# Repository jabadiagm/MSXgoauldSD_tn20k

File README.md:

# MSXgoauldSD_tn20k (DirectVideo branch)
MSX Goa'uld board with Tang Nano 20k and SD support

MSX2+ engine in Z80 socket. It turns one MSX into an MSX2+ by replacing Z80 processor. FPGA in board contains: 
* Z80
* V9958 with hdmi output
* MSX2+ BIOS
* SD Card support + Nextor 2.1
* 4MB mapper
* 2MB megaram SCC
* RTC
* PSG
* OPLL
* Kanji Level 1 & 2
* Wifi support using ESP (experimental)

## DirectVideo 240p output

Although the following inexpensive HDMI to VGA adapter is not documented to support 240p/480i input resolutions, there is actually a mode that makes it output a `15 kHz @ 59.9 Hz` sync RGBHV signal, compatible with consumer CRTs.

See [DirectVideo details](fpga/dv.md) to get more information.

## Boards

Old boards V1.4 and V4.1 are compatible with Goa'uld SD. V3 is not supported, owners of V3 should use Goa'uld standard firmware (0.80).

New pcb V1.5 is same as 1.4, optimized for online PCB assembly. See [Assembly guide](/pcba/pcba.md)

## Slot map

Mapper and megaram can be relocated to slots 1 or 2 using config menu.

## Megaram + Sofarun
Megaram is detected automatically by sofarun using default settings. When using other software you may need to indicate location, Slot 3-3 by default.

## Configuration
Config menu is showed pressing 'g' during MSX logo. New improved menu is created by [nataliapc](https://github.com/nataliapc/msx_goauld_settings_menu)

* Enable Mapper: On by default. Disable when having compatibility issues or to use a different mapper
* Enable Megaram: On by default. Disable when having compatibility issues or to use a different megaram
* Enable SD: On by default. Disable when using an external SD mapper
* Mapper Slot: 3 by default. Change to 1 or 2 to get mapper in a not expanded slot. Physical slot will be disabled
* Megaram Slot: 3 by default. Change to 1 or 2 to get megaram in a not expanded slot. Physical slot will be disabled
* Ghost SCC: Off by default. Enable to get sound from an SCC cartridge located in physical slot 1 or 2
* Enable Scanlines: On by default. Disable to get a clean hdmi picture
* Compatible Mode: Off by default. Enable if you experience crashes / unstabilities with external cartridges
* Turbo: Off by default. Enable to use an internal high-speed clock. Recommended for internal SD use only
* Save & Exit: store new config and continue, changes in mapper settings will be effective after pressing reset
* Save & Reset: store new config and make software reset, changes will be immediate

## Known issues
* Reset from config menu is not compatible with some hardware. Use physical reset button when possible
* Tape games fail: use poke -1,0
* Carnivore C2+ and Megaflashrom SCC+ SD are not compatible with Compatible mode (yes, I know)
* Wondertang is not compatible with Turbo mode
* Wifi unreliable: place ESP at appropiate distance from Tang

## Flashing
Programming is done in two steps:
* Flash firmware Z80_goauld.fs  

* Flash bios pack. Set Operation = "exFlash C Bin Erase, Program thru GAO-Bridge" and Start Address = 0x200000  

> [!WARNING]
> Not yet fully working on all MSX!
>

## Build instructions

```
export LD_PRELOAD=$(LIBFONT_CONFIG)
gw_sh build.tcl
```

## Flash Instructions

```
sudo openFPGALoader -b tangnano20k -f --verify impl/pnr/project.fs
```

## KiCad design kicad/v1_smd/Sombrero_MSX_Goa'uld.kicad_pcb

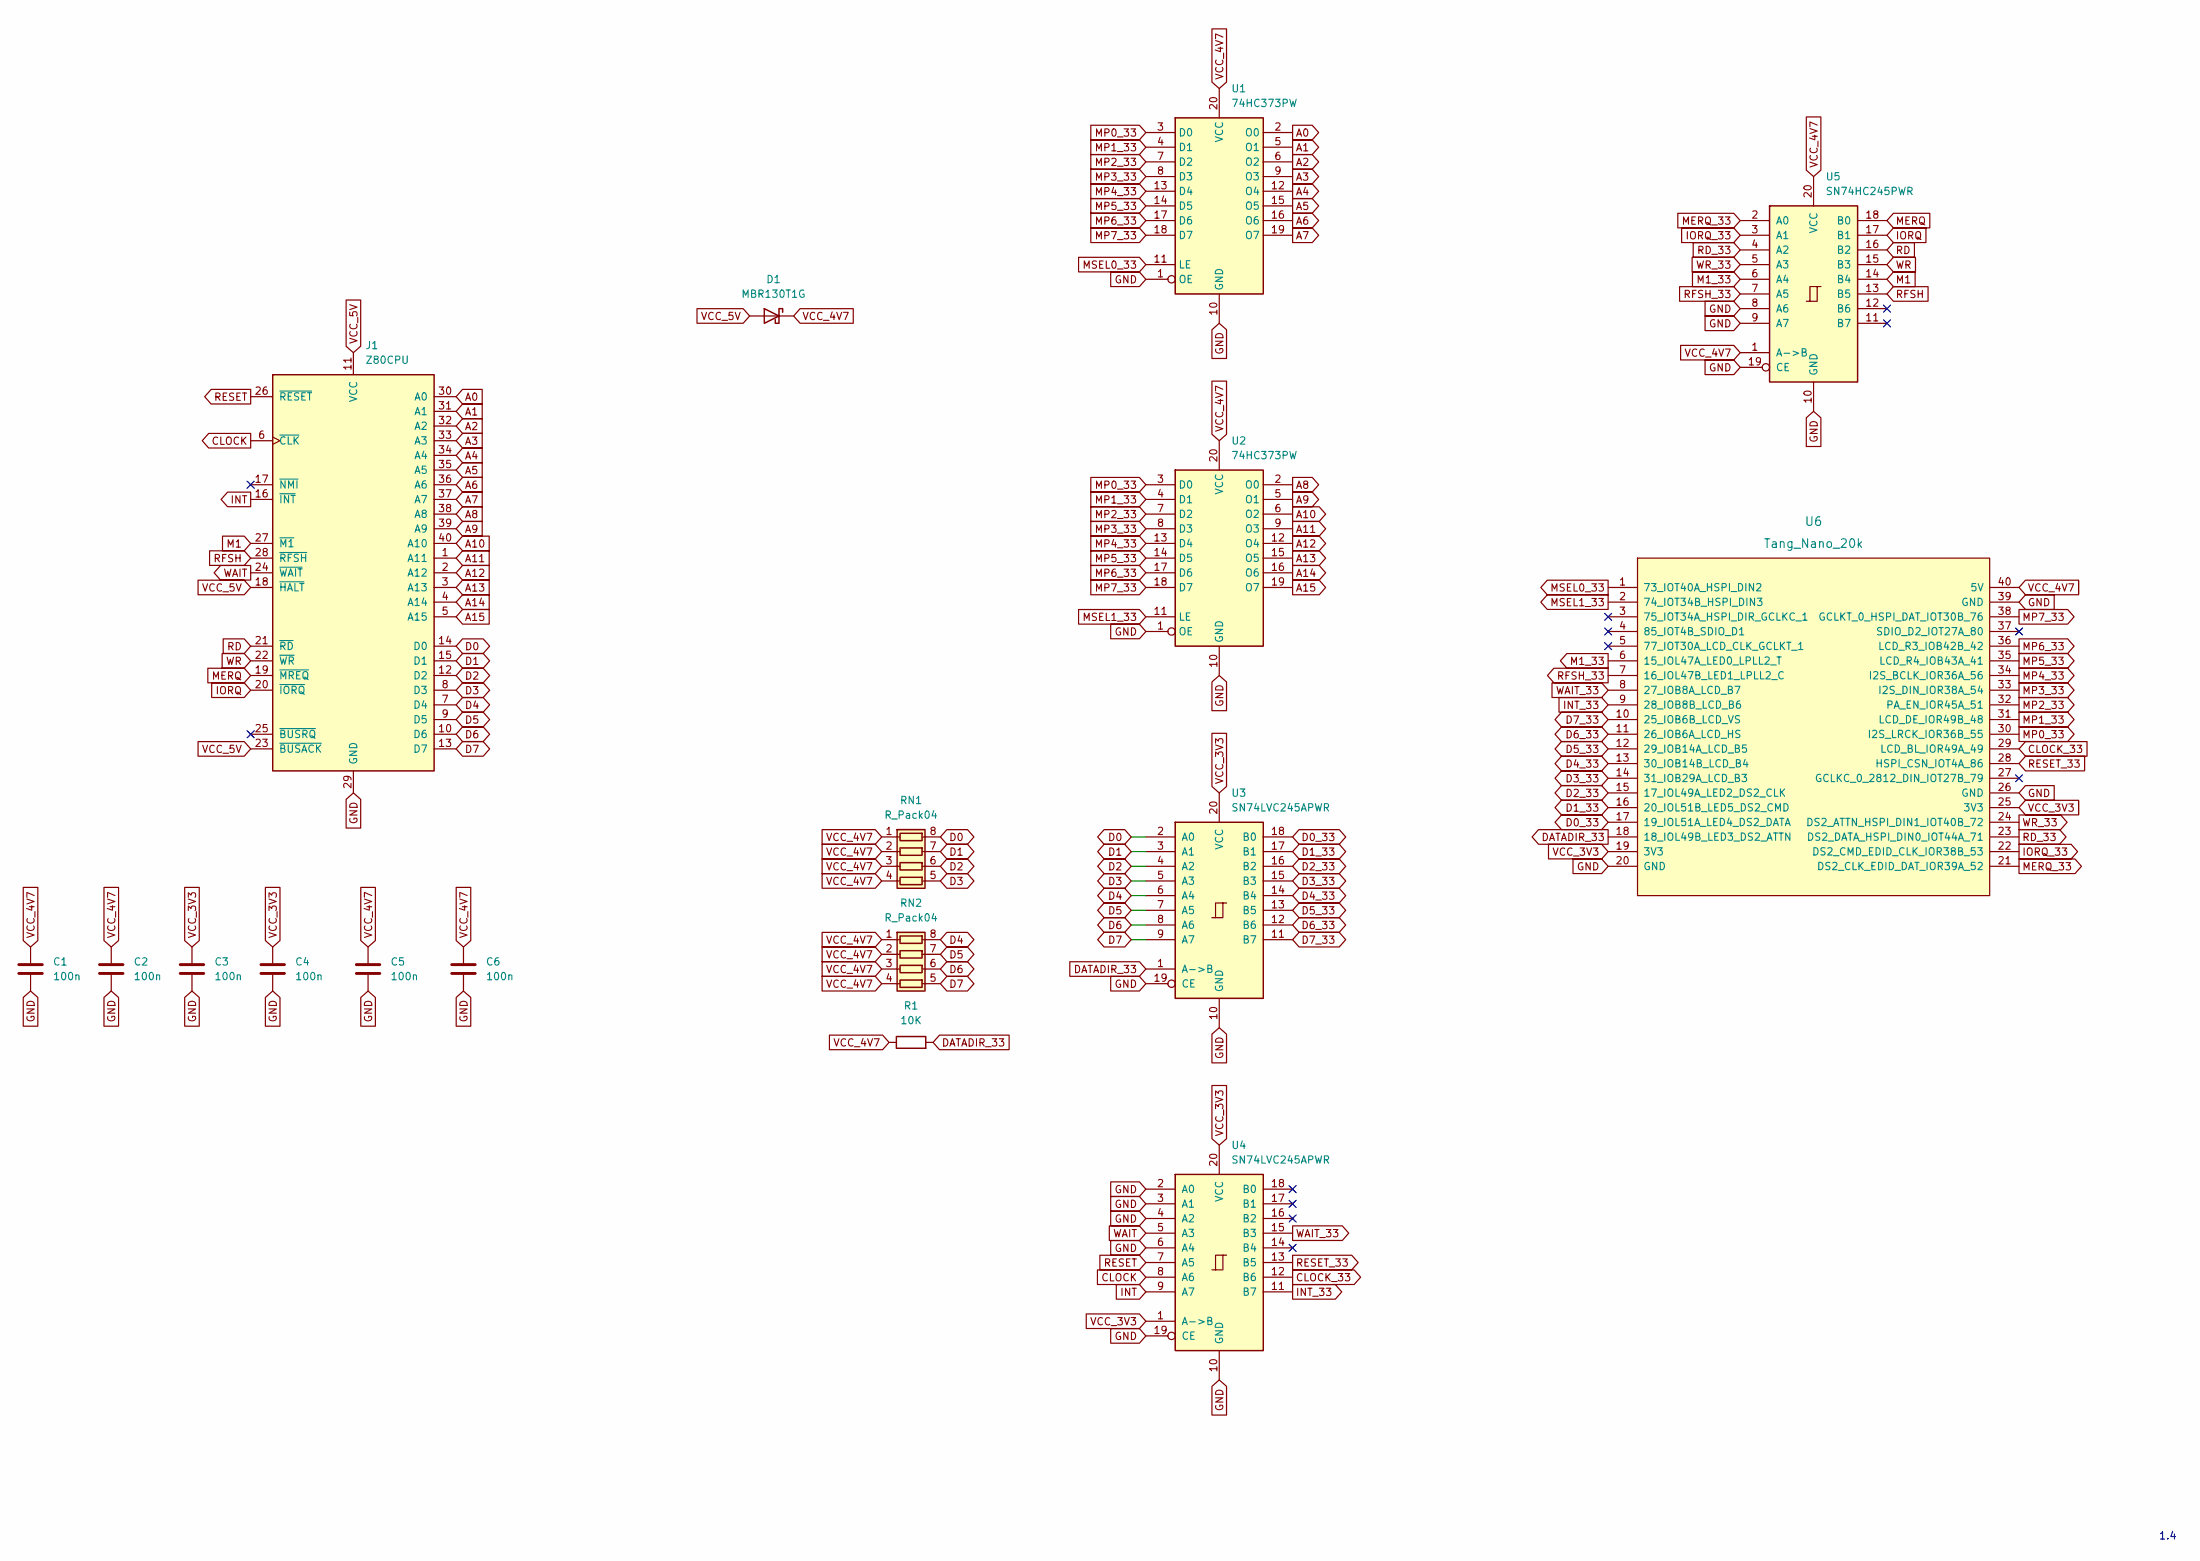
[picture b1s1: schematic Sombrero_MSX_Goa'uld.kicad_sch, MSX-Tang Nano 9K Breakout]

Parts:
C1, C2, C3, C4, C5, C6: 100n; C_0805_2012Metric; LCSC C49678
D1: MBR130T1G; D_SOD-123; LCSC C82461
J1: Z80CPU; DIP-40_W15.24mm_Socket
R1: 10K; R_0603_1608Metric; LCSC C15401
RN1, RN2: R_Pack04; R_Array_Convex_4x0603; LCSC C107374
U1, U2: 74HC373PW; TSSOP-20_4.4x6.5mm_P0.65mm; LCSC C132998
U3, U4: SN74LVC245APWR; TSSOP-20_4.4x6.5mm_P0.65mm; LCSC C7848
U5: SN74HC245PWR; TSSOP-20_4.4x6.5mm_P0.65mm; LCSC C37101
U6: Tang_Nano_20k

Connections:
A0: J1.30 (A0), U1.2 (O0)
A1: J1.31 (A1), U1.5 (O1)
A2: J1.32 (A2), U1.6 (O2)
A3: J1.33 (A3), U1.9 (O3)
A4: J1.34 (A4), U1.12 (O4)
A5: J1.35 (A5), U1.15 (O5)
A6: J1.36 (A6), U1.16 (O6)
A7: J1.37 (A7), U1.19 (O7)
A8: J1.38 (A8), U2.2 (O0)
A9: J1.39 (A9), U2.5 (O1)
A10: J1.40 (A10), U2.6 (O2)
A11: J1.1 (A11), U2.9 (O3)
A12: J1.2 (A12), U2.12 (O4)
A13: J1.3 (A13), U2.15 (O5)
A14: J1.4 (A14), U2.16 (O6)
A15: J1.5 (A15), U2.19 (O7)
CLOCK: J1.6 (~CLK), U4.8 (A6)
CLOCK_33: U4.12 (B6), U6.29 (LCD_BL_IOR49A_49)
D0: J1.14 (D0), RN1.8 (R1.2), U3.2 (A0)
D0_33: U3.18 (B0), U6.17 (19_IOL51A_LED4_DS2_DATA)
D1: J1.15 (D1), RN1.7 (R2.2), U3.3 (A1)
D1_33: U3.17 (B1), U6.16 (20_IOL51B_LED5_DS2_CMD)
D2: J1.12 (D2), RN1.6 (R3.2), U3.4 (A2)
D2_33: U3.16 (B2), U6.15 (17_IOL49A_LED2_DS2_CLK)
D3: J1.8 (D3), RN1.5 (R4.2), U3.5 (A3)
D3_33: U3.15 (B3), U6.14 (31_IOB29A_LCD_B3)
D4: J1.7 (D4), RN2.8 (R1.2), U3.6 (A4)
D4_33: U3.14 (B4), U6.13 (30_IOB14B_LCD_B4)
D5: J1.9 (D5), RN2.7 (R2.2), U3.7 (A5)
D5_33: U3.13 (B5), U6.12 (29_IOB14A_LCD_B5)
D6: J1.10 (D6), RN2.6 (R3.2), U3.8 (A6)
D6_33: U3.12 (B6), U6.11 (26_IOB6A_LCD_HS)
D7: J1.13 (D7), RN2.5 (R4.2), U3.9 (A7)
D7_33: U3.11 (B7), U6.10 (25_IOB6B_LCD_VS)
DATADIR_33: R1.2, U3.1 (A->B), U6.18 (18_IOL49B_LED3_DS2_ATTN)
GND: C1.2, C2.2, C3.2, C4.2, C5.2, C6.2, J1.29 (GND), U1.1 (OE), U1.10 (GND), U2.1 (OE), U2.10 (GND), U3.10 (GND), U3.19 (CE), U4.2 (A0), U4.3 (A1), U4.4 (A2), U4.6 (A4), U4.10 (GND), U4.19 (CE), U5.8 (A6), U5.9 (A7), U5.10 (GND), U5.19 (CE), U6.20 (GND), U6.26 (GND), U6.39 (GND)
INT: J1.16 (~INT), U4.9 (A7)
INT_33: U4.11 (B7), U6.9 (28_IOB8B_LCD_B6)
IORQ: J1.20 (~IORQ), U5.17 (B1)
IORQ_33: U5.3 (A1), U6.22 (DS2_CMD_EDID_CLK_IOR38B_53)
M1: J1.27 (~M1), U5.14 (B4)
M1_33: U5.6 (A4), U6.6 (15_IOL47A_LED0_LPLL2_T)
MERQ: J1.19 (~MREQ), U5.18 (B0)
MERQ_33: U5.2 (A0), U6.21 (DS2_CLK_EDID_DAT_IOR39A_52)
MP0_33: U1.3 (D0), U2.3 (D0), U6.30 (I2S_LRCK_IOR36B_55)
MP1_33: U1.4 (D1), U2.4 (D1), U6.31 (LCD_DE_IOR49B_48)
MP2_33: U1.7 (D2), U2.7 (D2), U6.32 (PA_EN_IOR45A_51)
MP3_33: U1.8 (D3), U2.8 (D3), U6.33 (I2S_DIN_IOR38A_54)
MP4_33: U1.13 (D4), U2.13 (D4), U6.34 (I2S_BCLK_IOR36A_56)
MP5_33: U1.14 (D5), U2.14 (D5), U6.35 (LCD_R4_IOB43A_41)
MP6_33: U1.17 (D6), U2.17 (D6), U6.36 (LCD_R3_IOB42B_42)
MP7_33: U1.18 (D7), U2.18 (D7), U6.38 (GCLKT_0_HSPI_DAT_IOT30B_76)
MSEL0_33: U1.11 (LE), U6.1 (73_IOT40A_HSPI_DIN2)
MSEL1_33: U2.11 (LE), U6.2 (74_IOT34B_HSPI_DIN3)
RD: J1.21 (~RD), U5.16 (B2)
RD_33: U5.4 (A2), U6.23 (DS2_DATA_HSPI_DIN0_IOT44A_71)
RESET: J1.26 (~RESET), U4.7 (A5)
RESET_33: U4.13 (B5), U6.28 (HSPI_CSN_IOT4A_86)
RFSH: J1.28 (~RFSH), U5.13 (B5)
RFSH_33: U5.7 (A5), U6.7 (16_IOL47B_LED1_LPLL2_C)
VCC_3V3: C3.1, C4.1, U3.20 (VCC), U4.1 (A->B), U4.20 (VCC), U6.19 (3V3), U6.25 (3V3)
VCC_4V7: C1.1, C2.1, C5.1, C6.1, D1.1 (K), R1.1, RN1.1 (R1.1), RN1.2 (R2.1), RN1.3 (R3.1), RN1.4 (R4.1), RN2.1 (R1.1), RN2.2 (R2.1), RN2.3 (R3.1), RN2.4 (R4.1), U1.20 (VCC), U2.20 (VCC), U5.1 (A->B), U5.20 (VCC), U6.40 (5V)
VCC_5V: D1.2 (A), J1.11 (VCC), J1.18 (~HALT), J1.23 (~BUSACK)
WAIT: J1.24 (~WAIT), U4.5 (A3)
WAIT_33: U4.15 (B3), U6.8 (27_IOB8A_LCD_B7)
WR: J1.22 (~WR), U5.15 (B3)
WR_33: U5.5 (A3), U6.24 (DS2_ATTN_HSPI_DIN1_IOT40B_72)

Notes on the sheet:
1.4

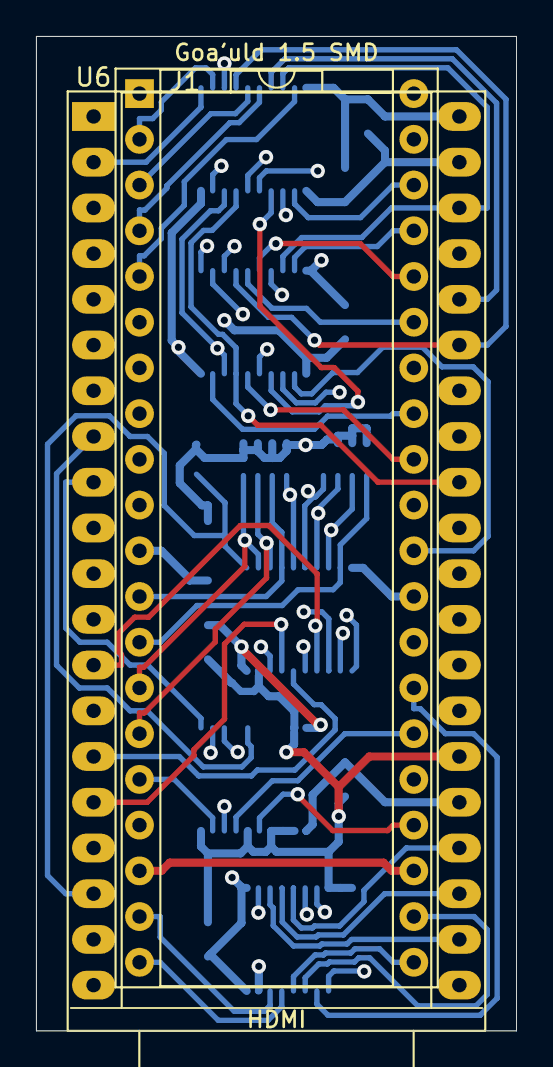
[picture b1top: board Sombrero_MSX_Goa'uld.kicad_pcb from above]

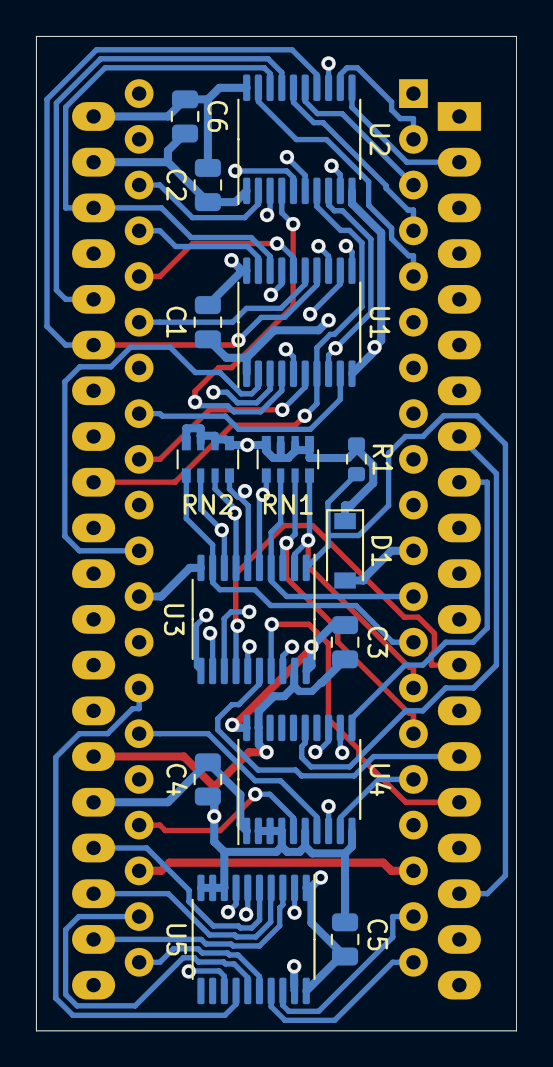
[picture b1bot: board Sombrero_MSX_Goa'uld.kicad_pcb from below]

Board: 4 copper layers, 26.7 x 55.2 mm, 17 parts (15 on the bottom side), 67 nets.

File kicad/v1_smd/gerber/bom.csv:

Designator,Footprint,Quantity,Value,LCSC Part #
"C1, C2, C3, C4, C5, C6",0805,6,100n,C49678
D1,D_SOD-123,1,MBR130T1G,C82461
J1,DIP-40_W15.24mm_Socket,1,Z80CPU,
R1,0603,1,10K,C15401
"RN1, RN2",R_Array_Convex_4x0603,2,R_Pack04,C107374
"U1, U2",TSSOP-20_4.4x6.5mm_P0.65mm,2,74HC373PW,C132998
"U3, U4",TSSOP-20_4.4x6.5mm_P0.65mm,2,SN74LVC245APWR,C7848
U5,TSSOP-20_4.4x6.5mm_P0.65mm,1,SN74HC245PWR,C37101
U6,Tang_Nano_20k,1,Tang_Nano_20k,

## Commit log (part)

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2025-08-06 Version FW 0.90 *Updated logic, sdram controller *Updated logic, included sdcard support *Updated logic, _req signals sync *Updated logic, psg noise filter *Removed module, scc+ fixed problem channel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
2025-08-06 Updated readme, included pcba guide
2025-08-06 updated pcba
2025-08-10 removed files
2025-08-29 Version FW 0.91 *Updated logic, slots map *Updated menu *Updated logic, boot menu before logo *Updated logic, main logic at 54 MHz *Include directive, swap slots 2,3
2026-01-24 Version FW 0.92 *Removed option SDRAM_32 *Updated logic memory_ctrl *Updated logic, rom loaded into sdram during boot *Fixed bug rtc *Updated logic, slot 0 expanded *Updated logic, included waitstate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
